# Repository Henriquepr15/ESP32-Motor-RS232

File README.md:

# ESP32 Motor RS232  

Projeto desenvolvido como parte de um teste prático para posição de Desenvolvedor de Hardware/Firmware.  

## Descrição  
Circuito com ESP32 para acionamento de motor a partir de sinal externo, utilizando reguladores de tensão, conversor buck LM2596, driver de motor e comunicação serial RS232 (MAX3232).  

## Funcionalidades  
- Leitura de sinal externo  
- Acionamento de motor por 10 segundos em nível baixo  
- Envio de mensagens de status via UART RS232  
- LEDs indicadores de funcionamento e debug  

## Estrutura do Projeto  
- Esquemáticos e PCB: Arquivos KiCad  
- Gerber, Drill, PnP e BOM: Saída de fabricação  
- Código em C: Arquivo main.c  
- Documentação: Datasheets e anotações  

## Requisitos de Software  
Código em linguagem C, leitura de entrada digital, controle de saída para o motor, temporização de 10 segundos e comunicação UART.  

## Como Compilar  
O código foi escrito em C padrão, podendo ser adaptado para o ESP32 com ESP-IDF ou Arduino IDE.  

## Requisitos de Hardware  
- ESP32-WROOM-32  
- LM2596 (buck converter)  
- AMS1117-3.3 (regulador LDO)  
- MAX3232 (interface RS232)  
- MOSFET AO3400A  
- Indutor, capacitores, resistores e conectores auxiliares  

## Autor  
Henrique Pires  

## Imagens do projeto

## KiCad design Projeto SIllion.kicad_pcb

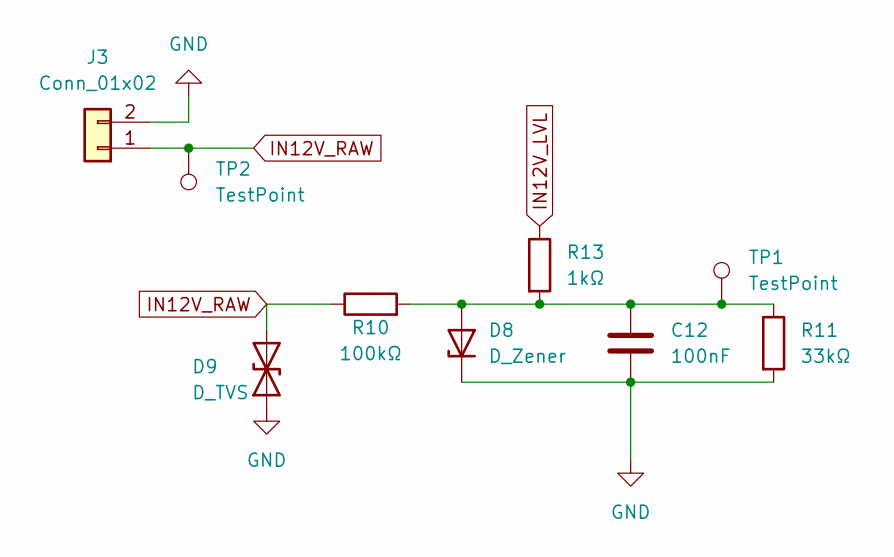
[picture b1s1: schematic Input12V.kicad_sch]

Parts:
C12: 100nF; C_0805_2012Metric
D8: D_Zener; D_SOD-123
D9: D_TVS; D_SMA
J3: Conn_01x02; PinHeader_1x02_P2.54mm_Vertical
R10: 100kΩ; R_0805_2012Metric
R11: 33kΩ; R_0805_2012Metric
R13: 1kΩ; R_0805_2012Metric
TP1, TP2: TestPoint; TestPoint_Pad_1.5x1.5mm

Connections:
GND: C12.2, D8.1 (K), D9.1 (A1), J3.2, R11.2; also elsewhere on the board
IN12V_LVL: R13.1; also elsewhere on the board
IN12V_RAW: D9.2 (A2), J3.1, R10.1, TP2.1
unnamed: C12.1, D8.2 (A), R10.2, R11.1, R13.2, TP1.1

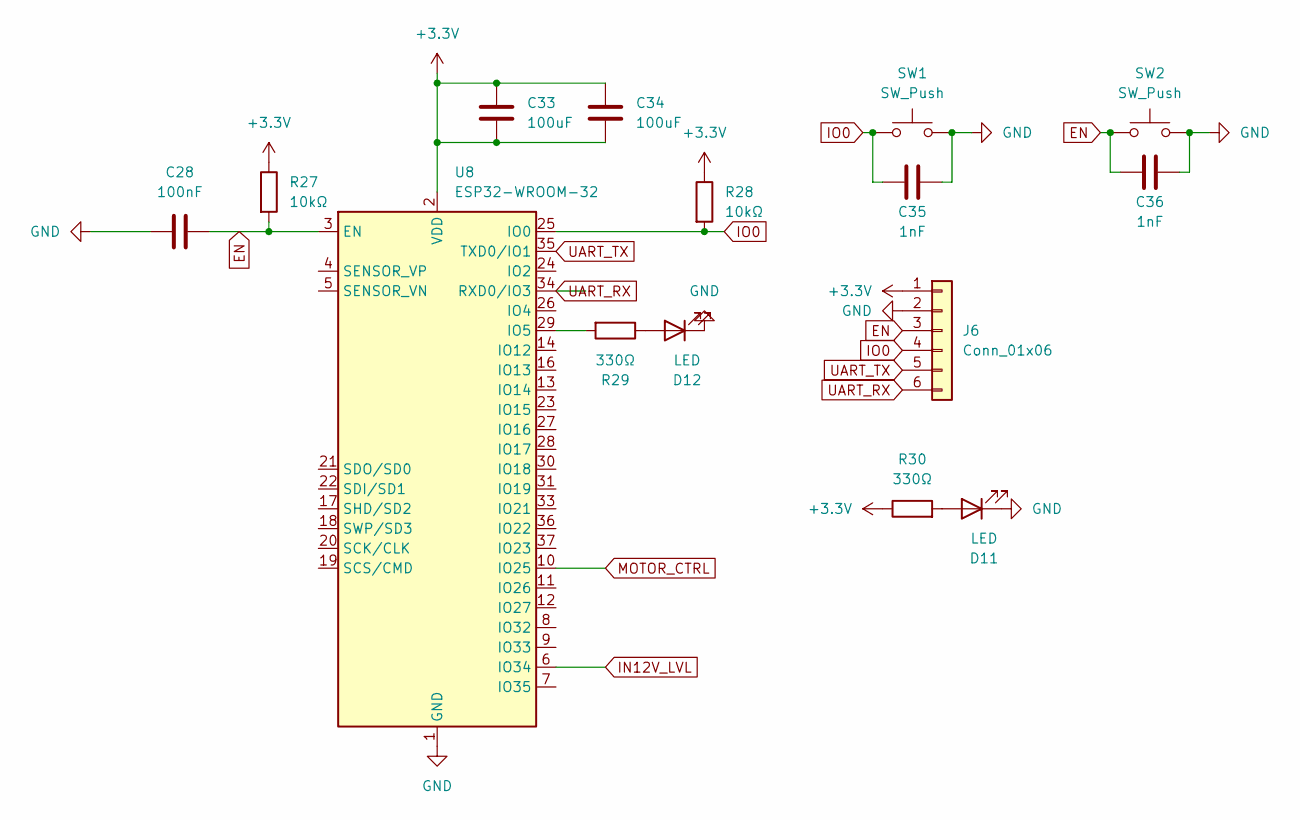
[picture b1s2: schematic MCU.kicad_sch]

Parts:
C28: 100nF; C_0805_2012Metric
C33, C34: 100uF; C_0805_2012Metric
C35, C36: 1nF; C_0805_2012Metric
D11, D12: LED; LED_0805_2012Metric
J6: Conn_01x06; PinHeader_1x06_P2.54mm_Vertical
R27, R28: 10kΩ; R_0805_2012Metric
R29, R30: 330Ω; R_0805_2012Metric
SW1, SW2: SW_Push; SW_SPST_TL3342
U8: ESP32-WROOM-32

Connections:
+3.3V: C33.1, C33.2, C34.1, C34.2, J6.1, R27.1, R28.1, R30.1, U8.2 (VDD); also elsewhere on the board
EN: C28.2, C36.1, J6.3, R27.2, SW2.1, U8.3 (EN)
GND: C28.1, C35.2, C36.2, D11.1 (K), D12.1 (K), J6.2, SW1.2, SW2.2, U8.1 (GND), U8.15 (GND), U8.38 (GND), U8.39 (GND); also elsewhere on the board
IN12V_LVL: U8.6 (IO34); also elsewhere on the board
IO0: C35.1, J6.4, R28.2, SW1.1, U8.25 (IO0)
MOTOR_CTRL: U8.10 (IO25); also elsewhere on the board
unnamed: D11.2 (A), R30.2
unnamed: D12.2 (A), R29.1
unnamed: R29.2, U8.29 (IO5)
UART_RX: J6.6, U8.34 (RXD0/IO3); also elsewhere on the board
UART_TX: J6.5, U8.35 (TXD0/IO1); also elsewhere on the board

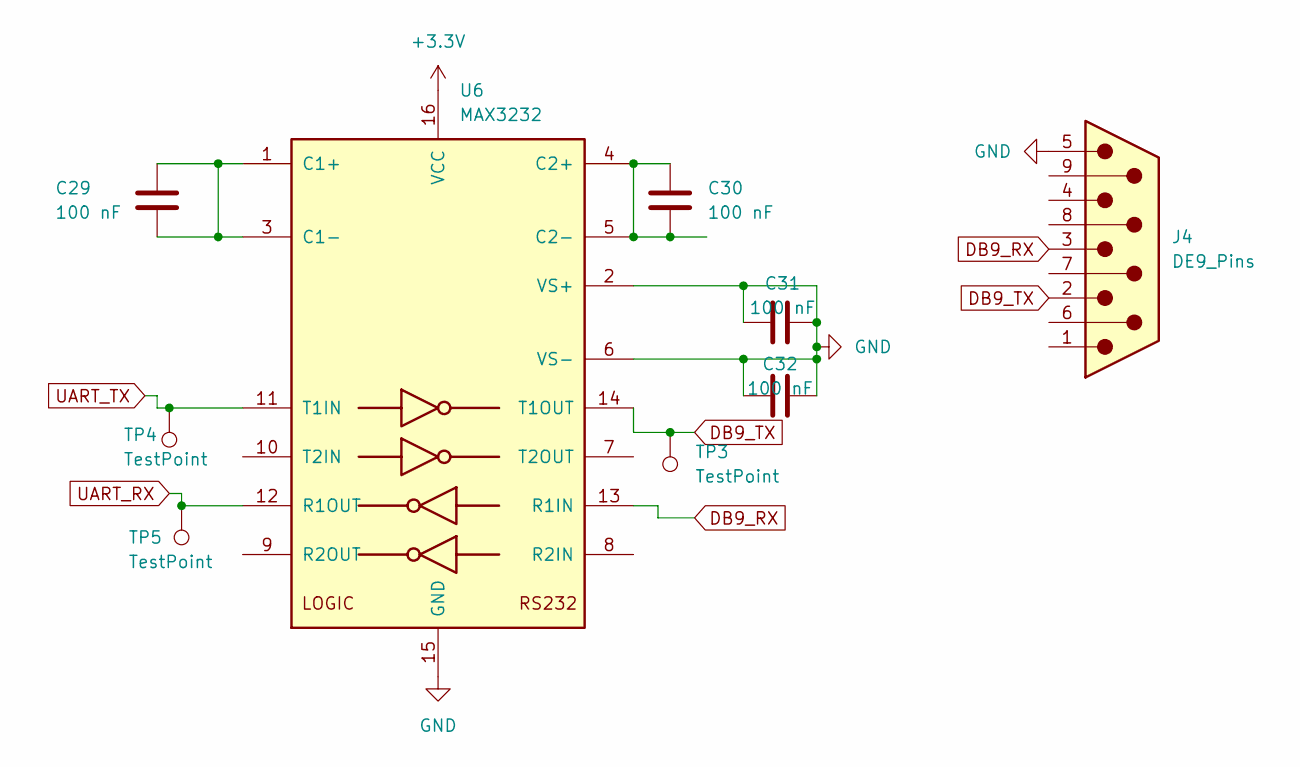
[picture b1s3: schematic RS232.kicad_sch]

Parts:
C29, C30, C31, C32: 100 nF; C_0805_2012Metric
J4: DE9_Pins; DSUB-9_Pins_Horizontal_P2.77x2.84mm_EdgePinOffset7.70mm_Hou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
TP3, TP4, TP5: TestPoint; TestPoint_Pad_1.5x1.5mm
U6: MAX3232; SOIC-16_3.9x9.9mm_P1.27mm

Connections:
+3.3V: U6.16 (VCC); also elsewhere on the board
DB9_RX: J4.3, U6.13 (R1IN)
DB9_TX: J4.2, TP3.1, U6.14 (T1OUT)
GND: C31.1, C31.2, C32.1, C32.2, J4.5, U6.2 (VS+), U6.6 (VS-), U6.15 (GND); also elsewhere on the board
unnamed: C29.1, C29.2, U6.1 (C1+), U6.3 (C1-)
unnamed: C30.1, C30.2, U6.4 (C2+), U6.5 (C2-)
UART_RX: TP5.1, U6.12 (R1OUT); also elsewhere on the board
UART_TX: TP4.1, U6.11 (T1IN); also elsewhere on the board

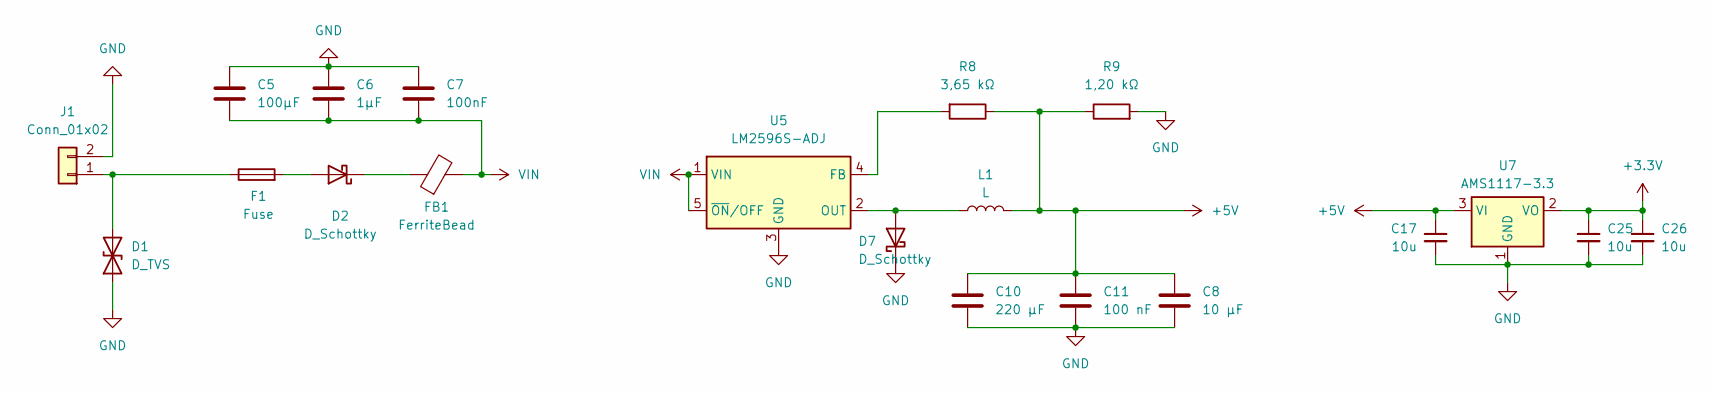
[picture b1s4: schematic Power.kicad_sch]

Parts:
C5: 100µF; C_0805_2012Metric
C6: 1µF; C_0805_2012Metric
C7: 100nF; C_0805_2012Metric
C8: 10 µF; C_0805_2012Metric
C10: 220 µF; C_0805_2012Metric
C11: 100 nF; C_0805_2012Metric
C17, C25, C26: 10u; C_0805_2012Metric; LCSC Part C15850
D1: D_TVS; D_SMA
D2, D7: D_Schottky; D_SMA
F1: Fuse; Fuse_1812_4532Metric
FB1: FerriteBead; L_0805_2012Metric
J1: Conn_01x02; PinHeader_1x02_P2.54mm_Vertical
L1: L; L_Bourns_SRN6045TA
R8: 3,65 kΩ; R_0805_2012Metric
R9: 1,20 kΩ; R_0805_2012Metric
U5: LM2596S-ADJ; TO-263-5_TabPin3
U7: AMS1117-3.3; SOT-223-3_TabPin2; LCSC Part C347222

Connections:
+3.3V: C25.1, C26.1, U7.2 (VO); also elsewhere on the board
+5V: C8.1, C10.1, C11.1, C17.1, L1.2, R8.1, R9.1, U7.3 (VI)
GND: C5.1, C6.1, C7.1, C8.2, C10.2, C11.2, C17.2, C25.2, C26.2, D1.1 (A1), D7.1 (K), J1.2, R9.2, U5.3 (GND), U7.1 (GND); also elsewhere on the board
unnamed: D1.2 (A2), F1.1, J1.1
unnamed: D2.2 (A), F1.2
unnamed: D2.1 (K), FB1.1
unnamed: D7.2 (A), L1.1, U5.2 (OUT)
unnamed: R8.2, U5.4 (FB)
VIN: C5.2, C6.2, C7.2, FB1.2, U5.1 (VIN), U5.5 (~ON/OFF)

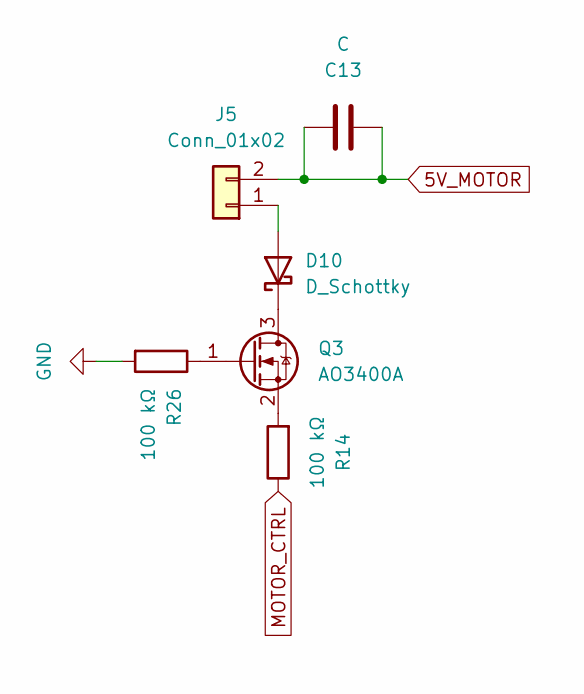
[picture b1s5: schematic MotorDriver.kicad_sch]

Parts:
C13: C; C_0805_2012Metric
D10: D_Schottky; D_SMA
J5: Conn_01x02; PinHeader_1x02_P2.54mm_Vertical
Q3: AO3400A; SOT-23
R14, R26: 100 kΩ; R_0805_2012Metric

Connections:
5V_MOTOR: C13.1, C13.2, J5.2
GND: R26.2; also elsewhere on the board
MOTOR_CTRL: R14.1; also elsewhere on the board
unnamed: D10.2 (A), J5.1
unnamed: D10.1 (K), Q3.3 (D)
unnamed: Q3.1 (G), R26.1
unnamed: Q3.2 (S), R14.2

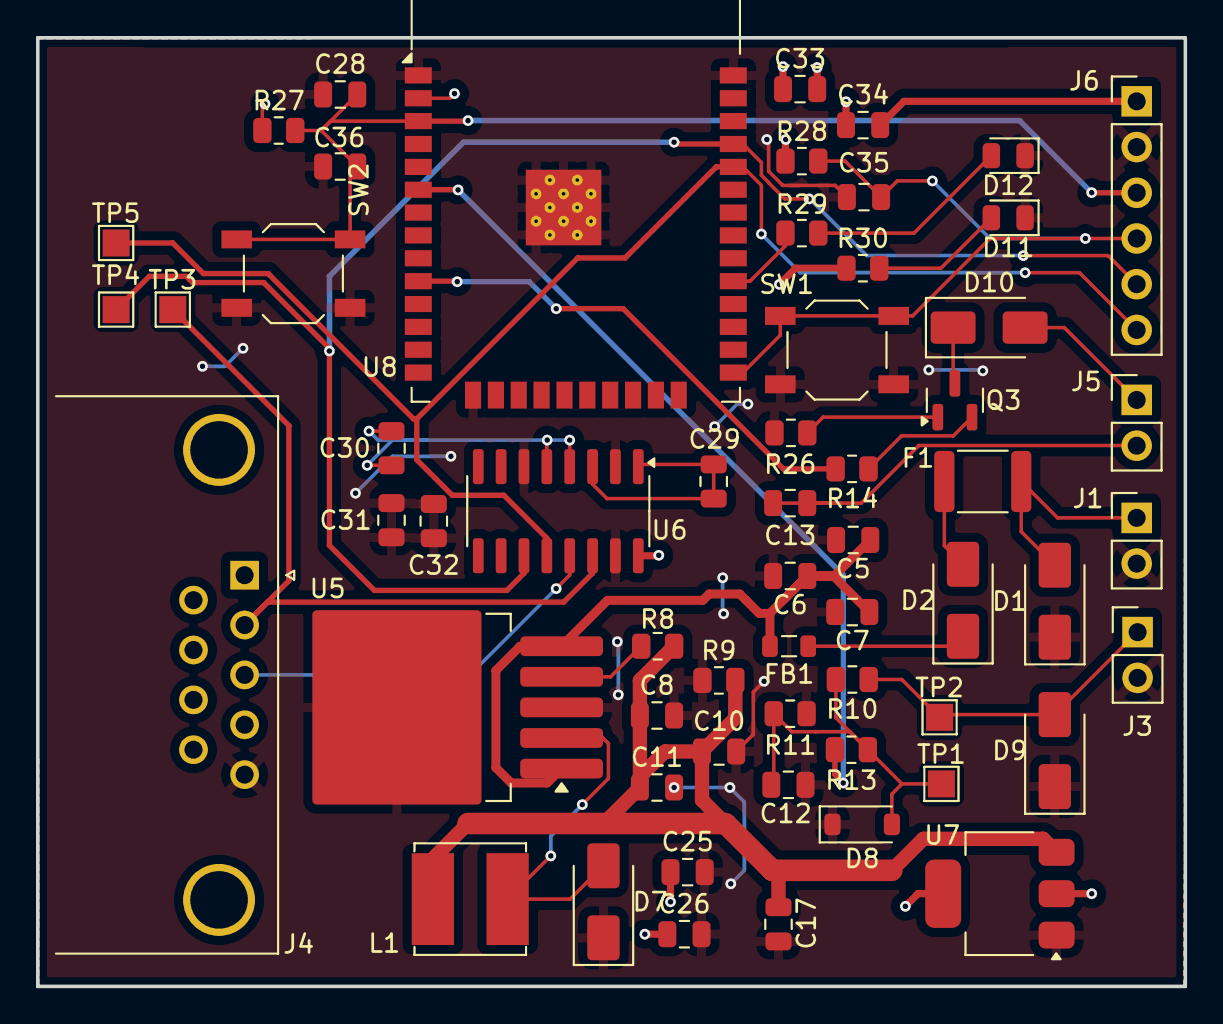
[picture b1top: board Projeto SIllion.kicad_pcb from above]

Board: 2 copper layers, 63.8 x 52.7 mm, 59 parts (0 on the bottom side), 29 nets.

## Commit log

2025-08-22 Atualiza projeto ESP32 Motor RS232
